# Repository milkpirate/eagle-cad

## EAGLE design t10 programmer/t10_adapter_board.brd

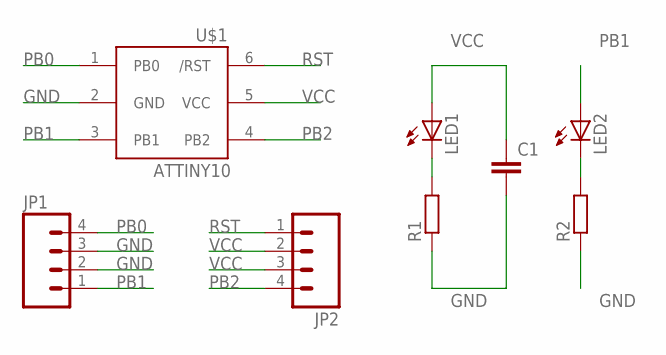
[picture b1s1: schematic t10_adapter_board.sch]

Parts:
C1: C-EUC0805K; C0805K
JP1, JP2: M04PTH; 1X04
LED1, LED2: LEDCHIPLED_0805; CHIPLED_0805
R1, R2: R-EU_R0805; R0805
U$1: ATTINY10; SOT23-6

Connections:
GND: C1.2, JP1.2, JP1.3, R1.1, R2.1, U$1.2 (GND)
unnamed: LED1.C, R1.2
unnamed: LED2.C, R2.2
PB0: JP1.4, U$1.1 (PB0)
PB1: JP1.1, LED2.A, U$1.3 (PB1)
PB2: JP2.4, U$1.4 (PB2)
RST: JP2.1, U$1.6 (/RST)
VCC: C1.1, JP2.2, JP2.3, LED1.A, U$1.5 (VCC)

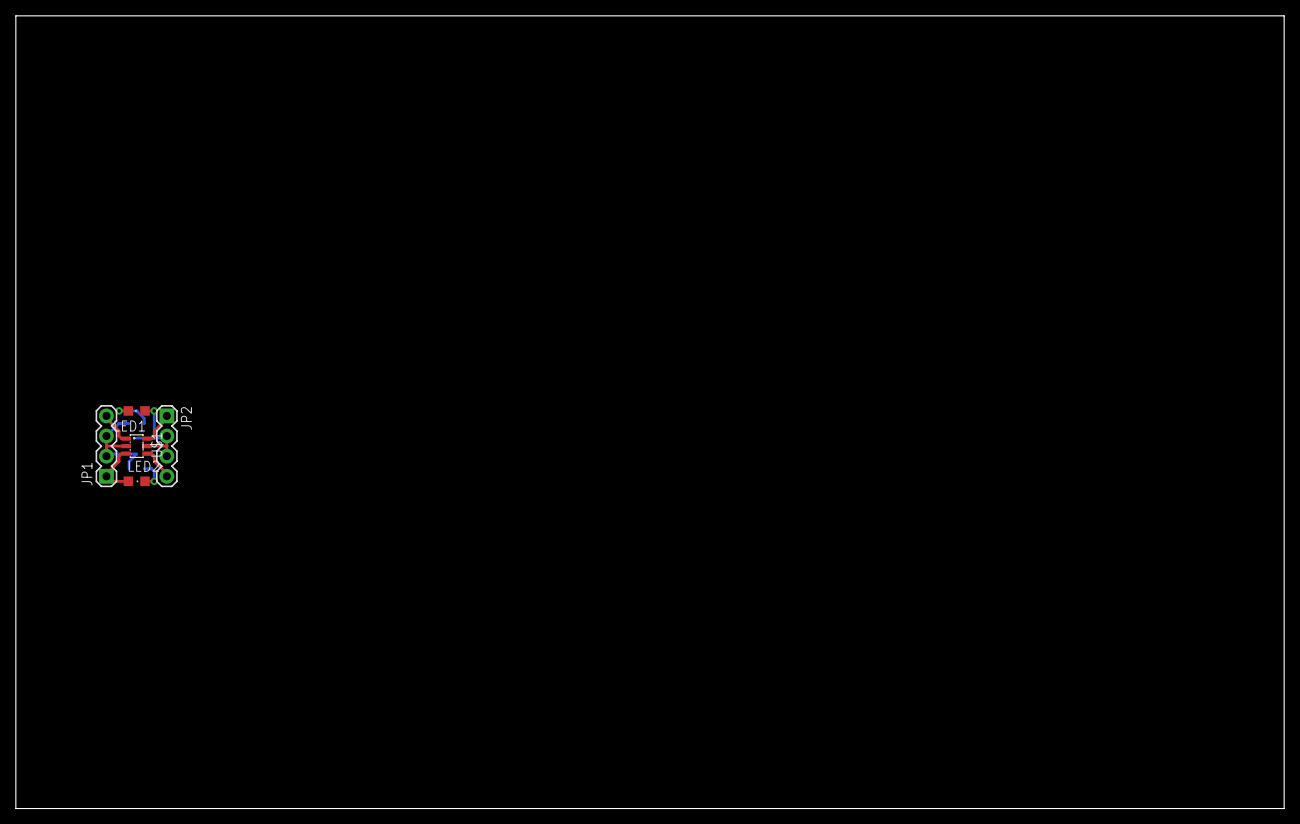
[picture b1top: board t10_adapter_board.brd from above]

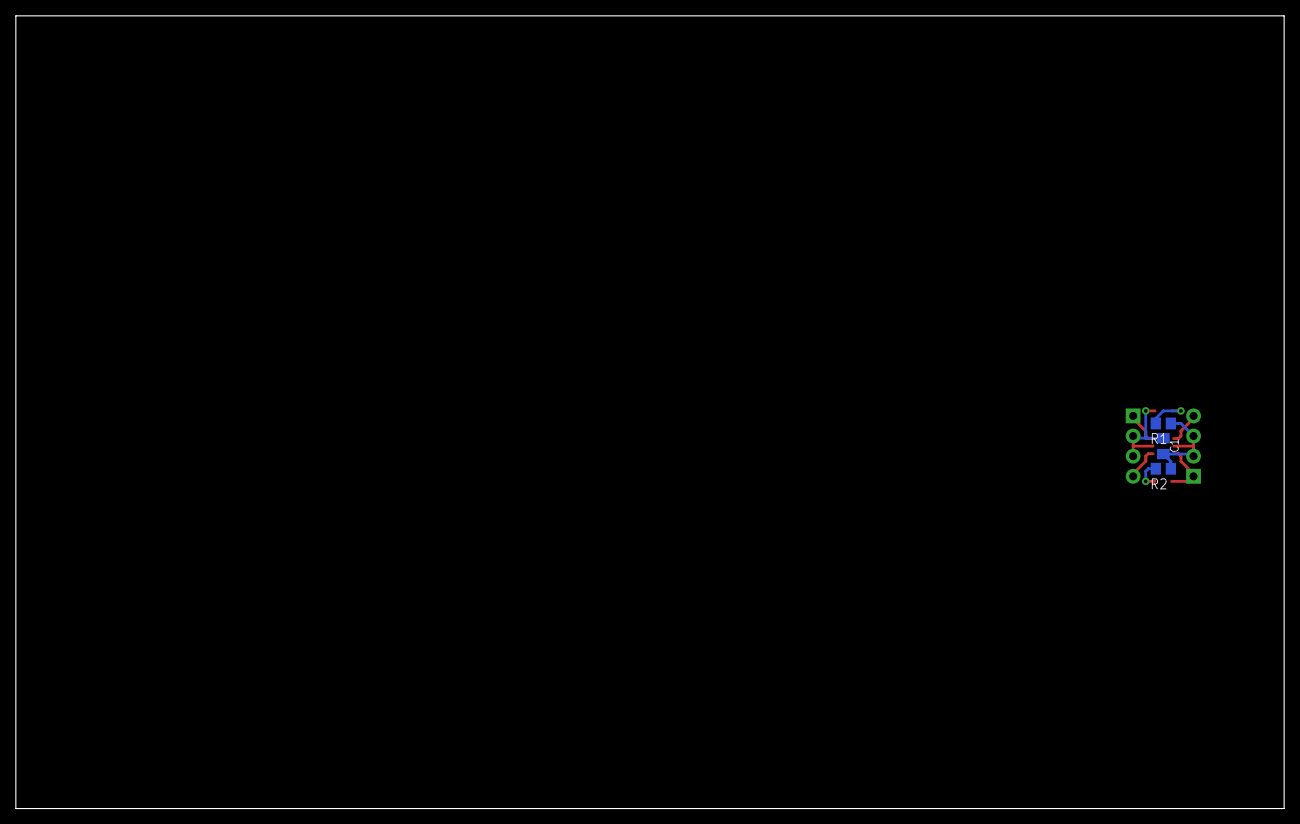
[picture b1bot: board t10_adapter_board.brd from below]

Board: 2 copper layers, 160.0 x 100.0 mm, 8 parts (3 on the bottom side), 8 nets.

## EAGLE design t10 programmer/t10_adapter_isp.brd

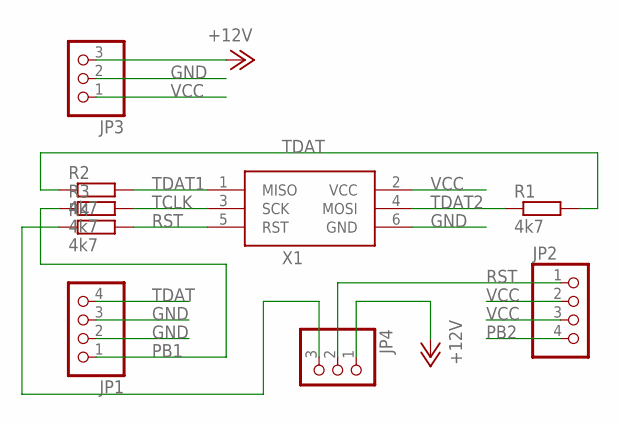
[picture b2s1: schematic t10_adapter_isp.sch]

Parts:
JP1, JP2: PINHD-1X4; 1X04
JP3, JP4: PINHD-1X3; 1X03
R1, R2, R3, R4: 4k7; M0805
X1: AVRISP-HEADER-6-SHROUDED; CONN-HARTING-ML6

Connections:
+12V: JP3.3, JP4.1
GND: JP1.2, JP1.3, JP3.2, X1.6 (GND)
unnamed: JP4.3, R4.1
PB1: JP1.1, R3.1
PB2: JP2.4
RST: JP2.1, JP4.2, R4.2, X1.5 (RST)
TCLK: R3.2, X1.3 (SCK)
TDAT: JP1.4, R1.2, R2.1
TDAT1: R2.2, X1.1 (MISO)
TDAT2: R1.1, X1.4 (MOSI)
VCC: JP2.2, JP2.3, JP3.1, X1.2 (VCC)

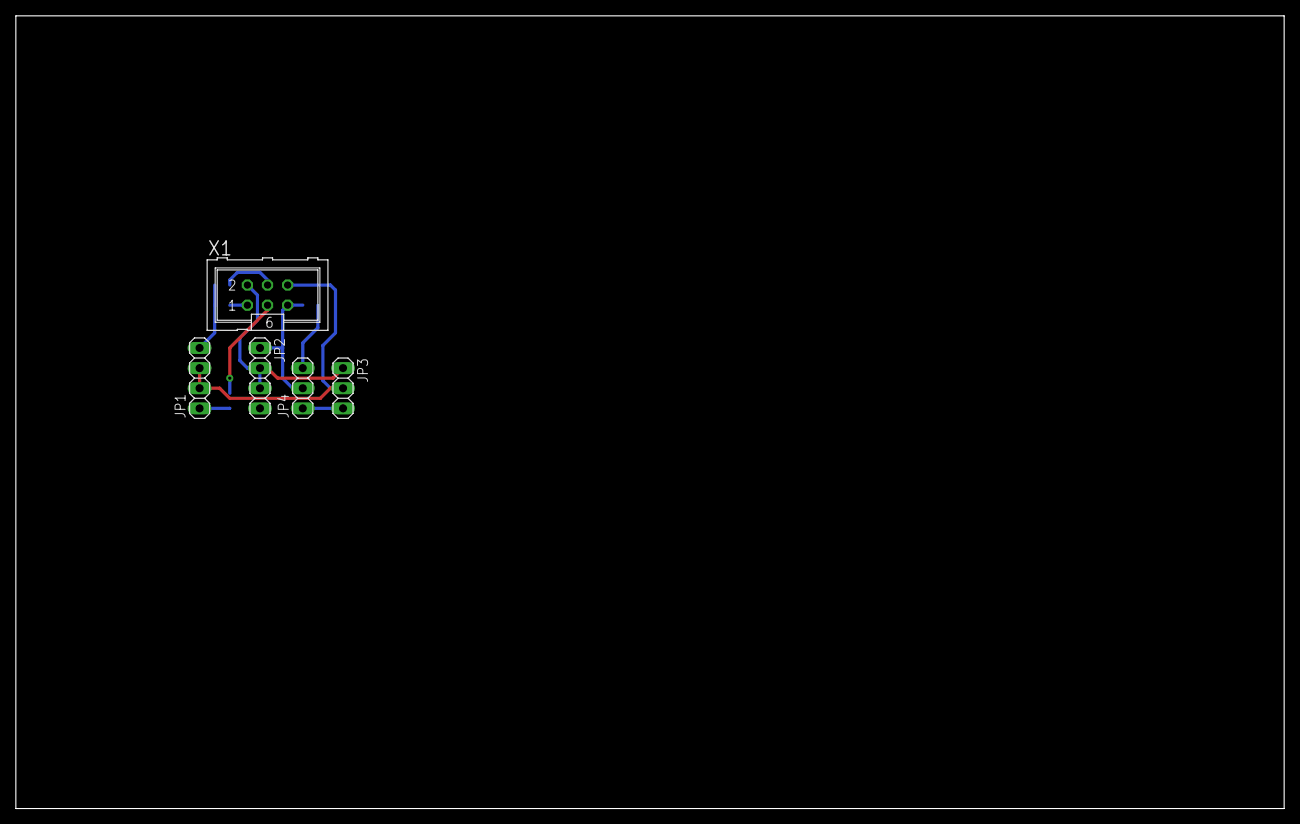
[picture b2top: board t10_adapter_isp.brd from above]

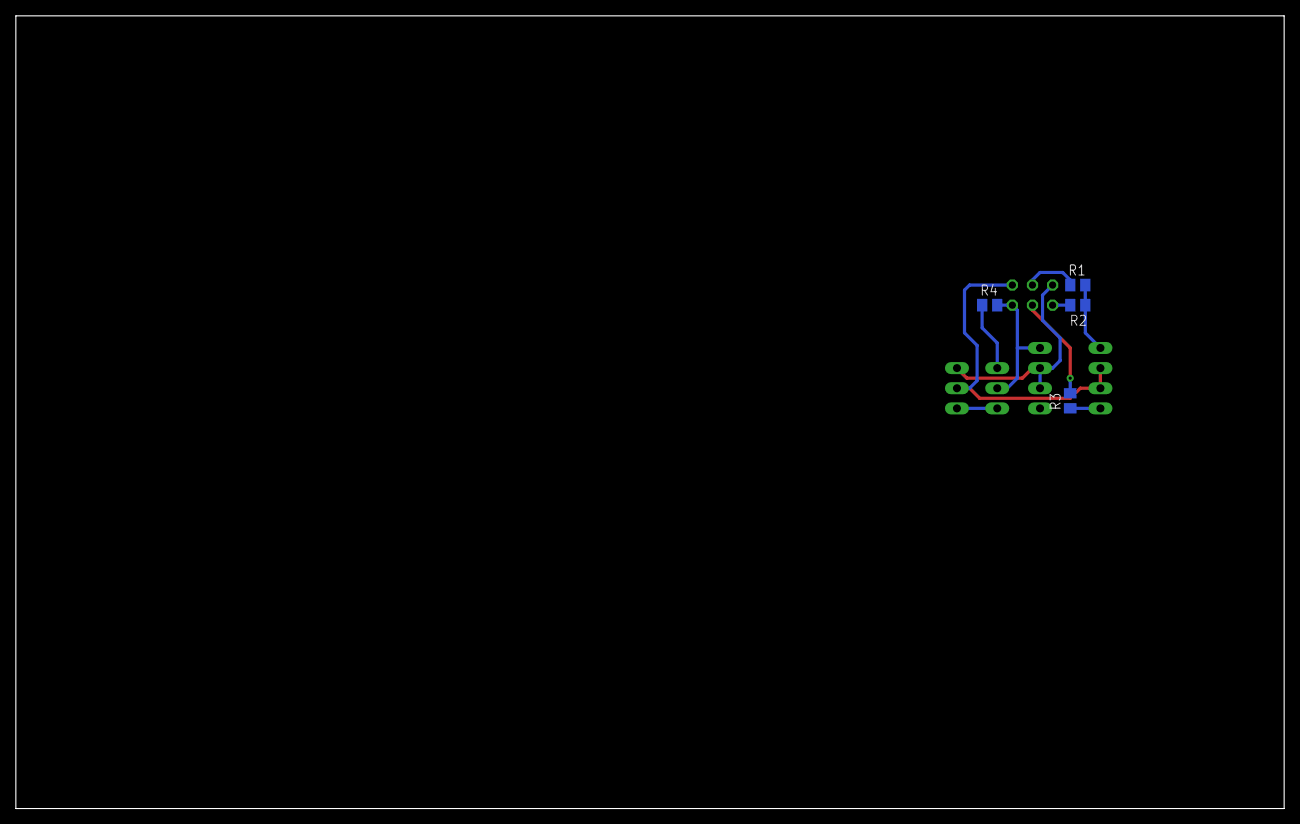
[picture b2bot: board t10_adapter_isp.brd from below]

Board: 2 copper layers, 160.0 x 100.0 mm, 9 parts (4 on the bottom side), 10 nets.

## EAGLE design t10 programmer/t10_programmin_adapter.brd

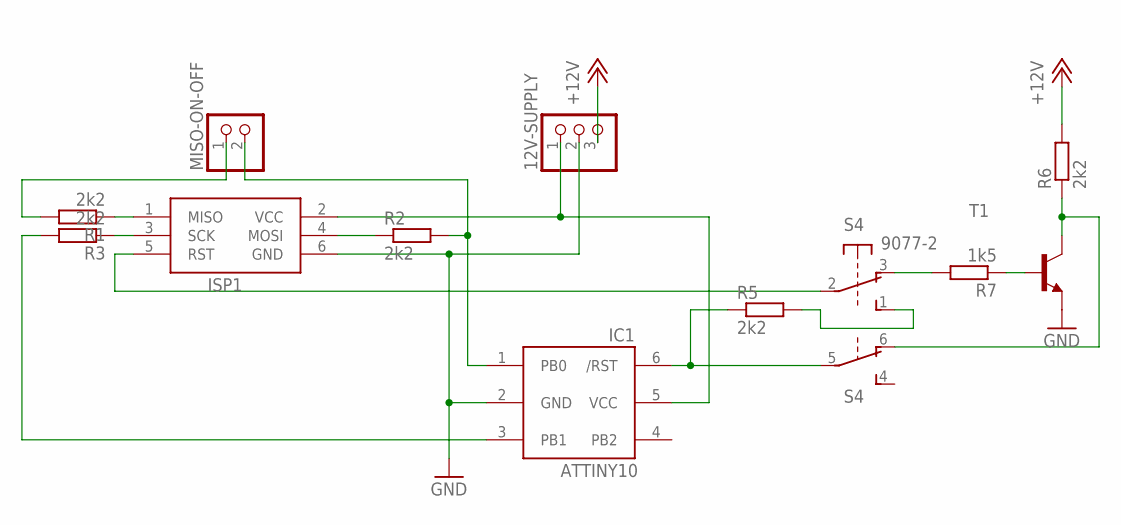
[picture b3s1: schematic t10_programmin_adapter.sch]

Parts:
12V-SUPPLY: PINHD-1X3/90; 1X03/90
IC1: ATTINY10; SOT23-6
ISP1: AVRISP-6; AVRISP
MISO-ON-OFF: PINHD-1X2; 1X02
R1, R2, R3, R5, R6: 2k2; 0204/7
R7: 1k5; 0207/2V
S4: 9077-2
T1: 2N6517-NPN-TO92-CBE; TO92-CBE

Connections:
+12V: 12V-SUPPLY.3, R6.2
GND: 12V-SUPPLY.2, IC1.2 (GND), ISP1.6 (GND), T1.E
ISP-MISO: ISP1.1 (MISO), R1.1
ISP-MOSI: ISP1.4 (MOSI), R2.1
ISP-RST: ISP1.5 (RST), S4.2
ISP-SCK: ISP1.3 (SCK), R3.1
MISO: MISO-ON-OFF.1, R1.2
unnamed: R6.1, S4.6 (O), T1.C
unnamed: R7.1, T1.B
unnamed: R7.2, S4.3 (O)
unnamed: R5.2, S4.1 (S)
RST: IC1.6 (/RST), R5.1, S4.5
SCK: IC1.3 (PB1), R3.2
TDIDATA: IC1.1 (PB0), MISO-ON-OFF.2, R2.2
VCC: 12V-SUPPLY.1, IC1.5 (VCC), ISP1.2 (VCC)

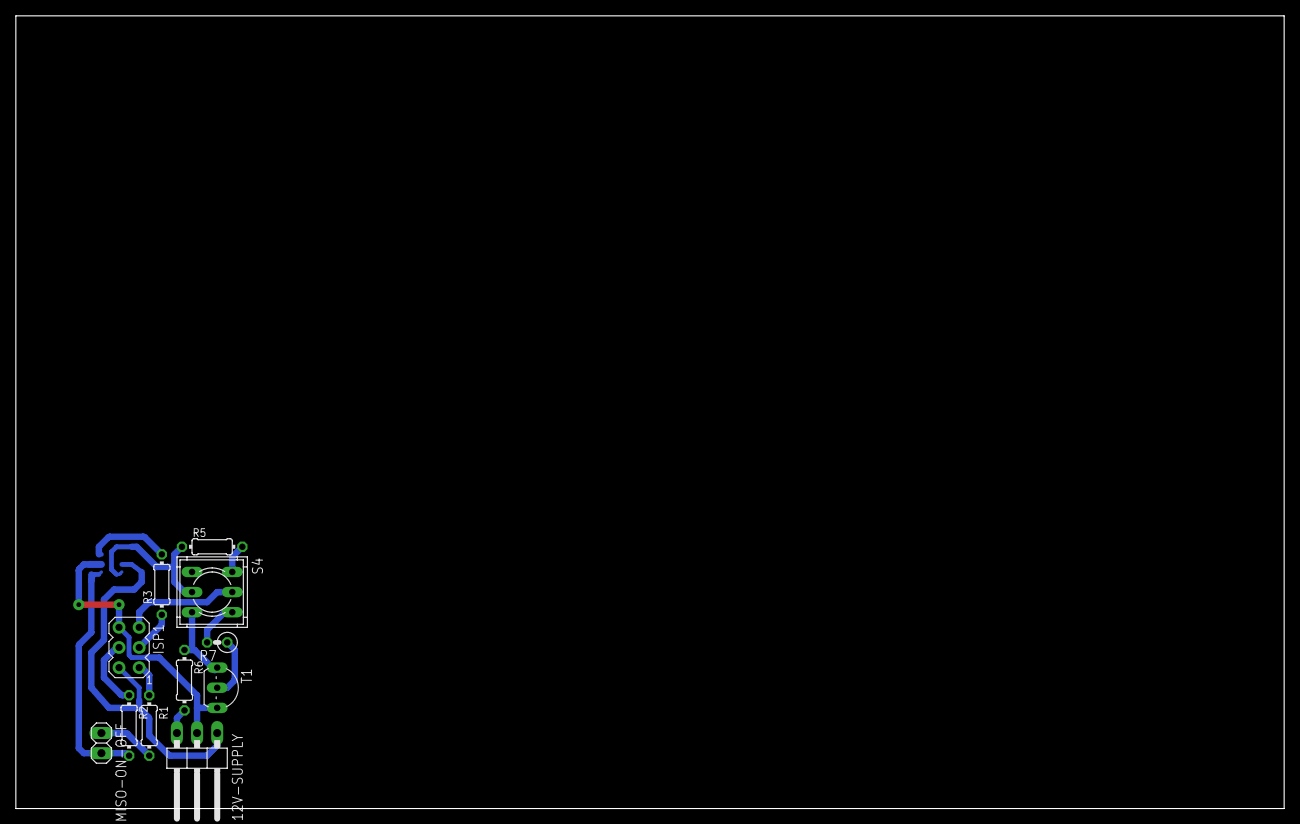
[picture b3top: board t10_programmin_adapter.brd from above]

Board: 2 copper layers, 160.0 x 100.0 mm, 12 parts (1 on the bottom side), 15 nets.

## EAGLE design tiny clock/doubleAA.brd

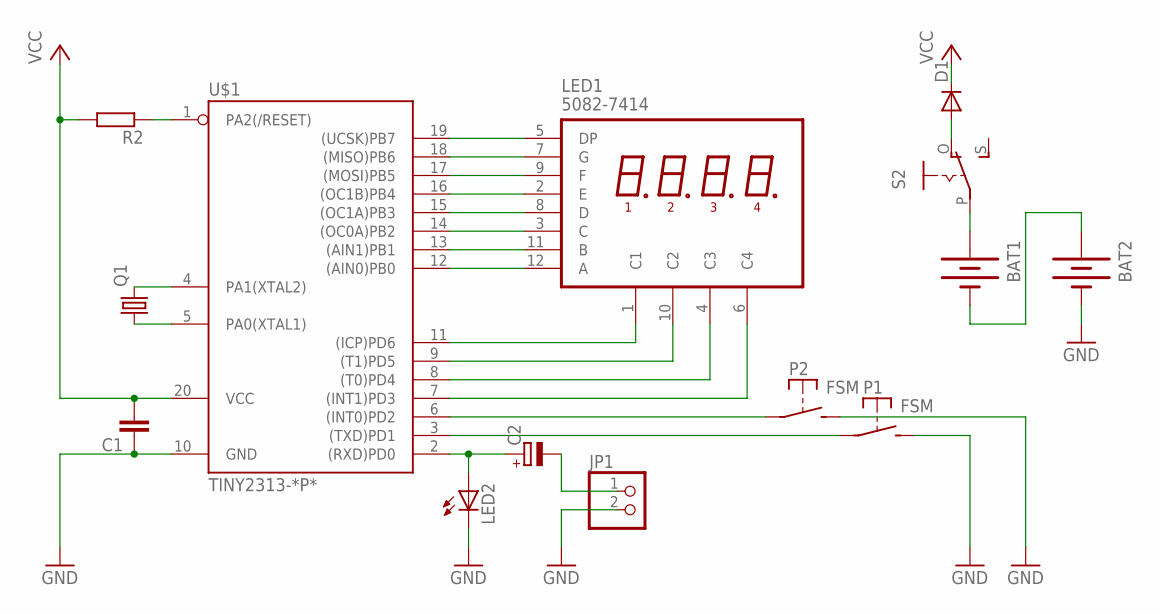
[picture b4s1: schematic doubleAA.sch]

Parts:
BAT1, BAT2: BATTERYAA-PANEL; BATTERY-AA-PANEL
C1: C-EU025-024X044; C025-024X044
C2: CPOL-EUE2,5-6E; E2,5-6E
D1: DIODE-D-5; D-5
JP1: PINHD-1X2; 1X02
LED1: 5082-7414
LED2: LED5MM
P1, P2: FSM
Q1: CRYSTALTC26H; TC26H
R2: R-EU_0204/7; 0204/7
S2: EG1218S; EG1218
U$1: TINY2313-*P*; DIL20

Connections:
GND: BAT2.-, C1.1, JP1.2, LED2.K (C), P1.P$2 (S), P2.P$2 (S), U$1.10 (GND)
unnamed: LED1.5 (DP), U$1.19 ((UCSK)PB7)
unnamed: LED1.7 (G), U$1.18 ((MISO)PB6)
unnamed: LED1.9 (F), U$1.17 ((MOSI)PB5)
unnamed: LED1.2 (E), U$1.16 ((OC1B)PB4)
unnamed: LED1.8 (D), U$1.15 ((OC1A)PB3)
unnamed: LED1.3 (C), U$1.14 ((OC0A)PB2)
unnamed: LED1.11 (B), U$1.13 ((AIN1)PB1)
unnamed: LED1.12 (A), U$1.12 ((AIN0)PB0)
unnamed: LED1.1 (C1), U$1.11 ((ICP)PD6)
unnamed: LED1.10 (C2), U$1.9 ((T1)PD5)
unnamed: LED1.4 (C3), U$1.8 ((T0)PD4)
unnamed: LED1.6 (C4), U$1.7 ((INT1)PD3)
unnamed: Q1.2, U$1.4 (PA1(XTAL2))
unnamed: Q1.1, U$1.5 (PA0(XTAL1))
unnamed: P2.P$1, U$1.6 ((INT0)PD2)
unnamed: P1.P$1, U$1.3 ((TXD)PD1)
unnamed: R2.1, U$1.1 (PA2(/RESET))
unnamed: BAT1.+, S2.P
unnamed: C2.+, LED2.A, U$1.2 ((RXD)PD0)
unnamed: C2.-, JP1.1
unnamed: D1.A, S2.O
unnamed: BAT1.-, BAT2.+
VCC: C1.2, D1.C, R2.2, U$1.20 (VCC)

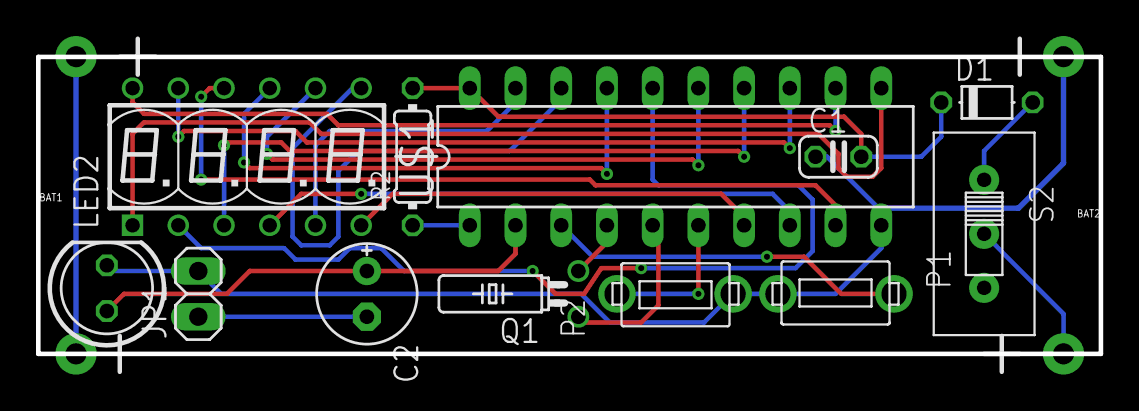
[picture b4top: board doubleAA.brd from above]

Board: 2 copper layers, 59.0 x 16.5 mm, 14 parts (0 on the bottom side), 24 nets.

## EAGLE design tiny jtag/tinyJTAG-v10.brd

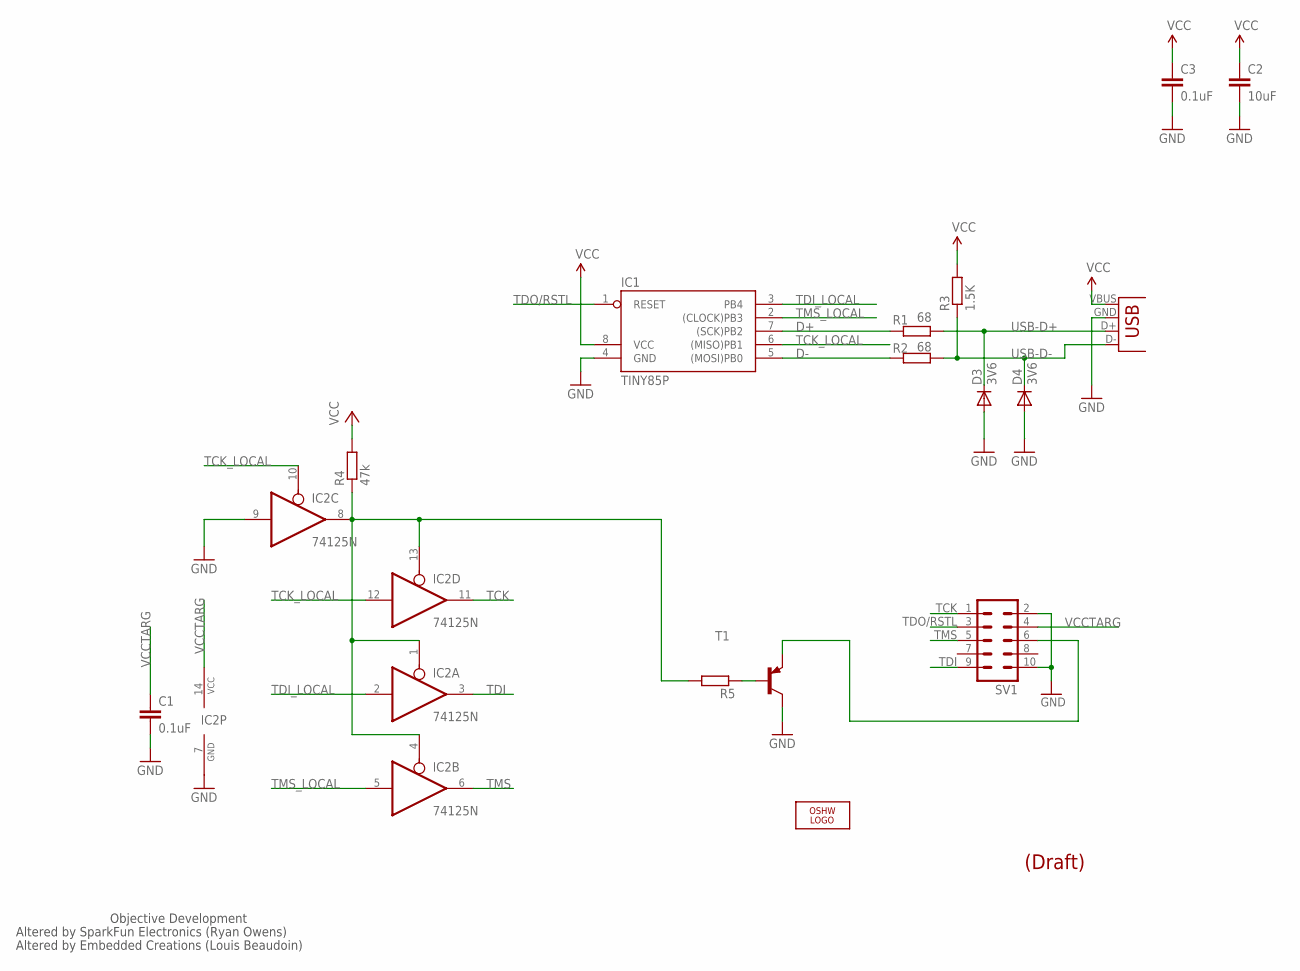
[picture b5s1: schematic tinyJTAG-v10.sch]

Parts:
C1: 0.1uF; CAP-PTH-SMALL2
C2: 10uF; C025-025X050
C3: 0.1uF; CAP-PTH-SMALL
D3: 3V6; D-2.5
D4: 3V6; D-5
IC1: TINY85P; DIL08
IC2: 74125N; DIL14
LOGO1: OSHW_LOGO_FILLX0150-NT; OSHW_FILLX150_NOTEXT
R1, R2: 68; 0207/2V
R3: 1.5K; 0207/2V
R4: 47k; 0207/7
R5: R-EU_0207/7; 0207/7
SV1: ML10
T1: BC327-16-PNP-TO92-EBC; TO92-EBC
X1: USB-A-H

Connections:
D+: IC1.7 ((SCK)PB2), R1.2
D-: IC1.5 ((MOSI)PB0), R2.2
GND: C1.2, C2.2, C3.2, D3.A, D4.A, IC1.4 (GND), IC2.7 (GND), IC2.9 (I), SV1.2, SV1.10, T1.C, X1.GND (VBUS)
unnamed: IC2.1 (OE), IC2.4 (OE), IC2.8 (O), IC2.13 (OE), R4.1, R5.2
unnamed: SV1.6, T1.E
unnamed: R5.1, T1.B
TCK: IC2.11 (O), SV1.1
TCK_LOCAL: IC1.6 ((MISO)PB1), IC2.10 (OE), IC2.12 (I)
TDI: IC2.3 (O), SV1.9
TDI_LOCAL: IC1.3 (PB4), IC2.2 (I)
TDO/RSTL: IC1.1 (RESET), SV1.3
TMS: IC2.6 (O), SV1.5
TMS_LOCAL: IC1.2 ((CLOCK)PB3), IC2.5 (I)
USB-D+: D3.C, R1.1, X1.D+ (D-)
USB-D-: D4.C, R2.1, R3.1, X1.D- (D+)
VCC: C2.1, C3.1, IC1.8 (VCC), R3.2, R4.2, X1.VBUS (GND)
VCCTARG: C1.1, IC2.14 (VCC), SV1.4

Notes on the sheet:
Objective Development
Altered by SparkFun Electronics (Ryan Owens)
Altered by Embedded Creations (Louis Beaudoin)
(Draft)

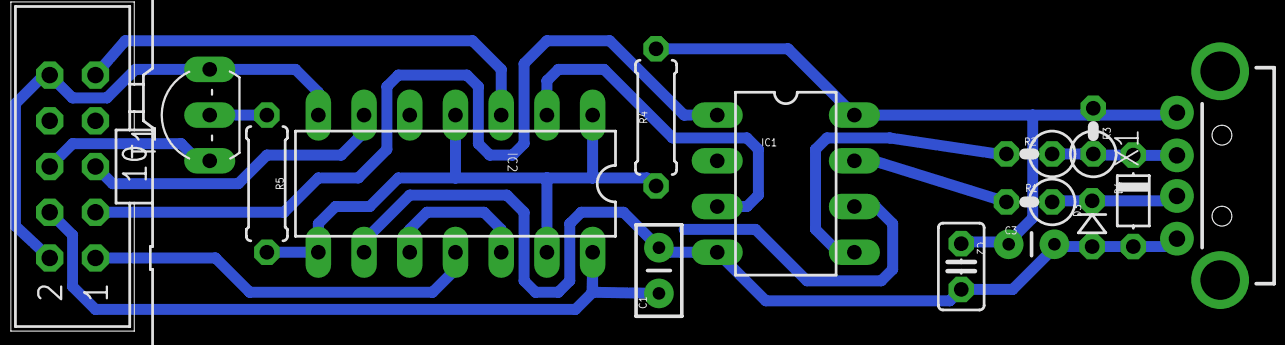
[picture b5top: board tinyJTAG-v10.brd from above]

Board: 2 copper layers, 16 parts (1 on the bottom side), 17 nets.

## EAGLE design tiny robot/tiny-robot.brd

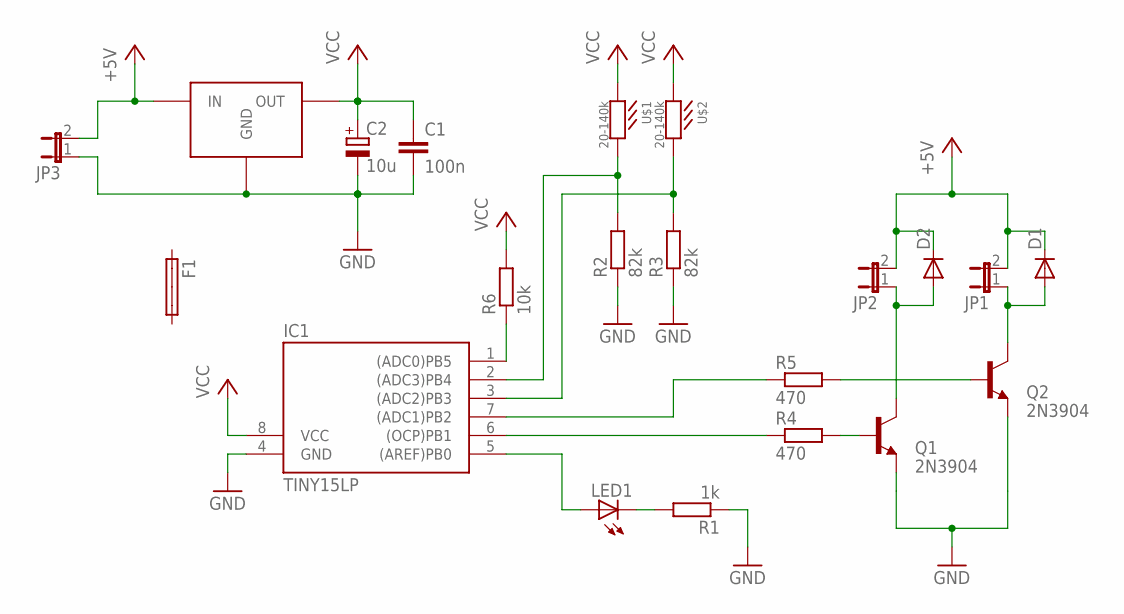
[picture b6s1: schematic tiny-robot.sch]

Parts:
C1: 100n; C025-025X050
C2: 10u; E2,5-6E
D1, D2: 1N4148DO35-7; DO35-7
F1: SHK20L
IC1: TINY15LP; DIL08
JP1, JP2, JP3: JP1E; JP1
LED1: LED3MM
Q1, Q2: 2N3904; TO92
R1: 1k; 0207/2V
R2, R3: 82k; 0207/5V
R4: 470; 0207/2V
R5: 470; 0207/5V
R6: 10k; 0207/5V
U$1, U$2: 20-140k; LDR-906014
U$3: MCP1700; TO92

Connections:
+5V: D1.C, D2.C, JP1.2, JP2.2, JP3.2, U$3.2 (IN)
GND: C1.2, C2.-, IC1.4 (GND), JP3.1, Q1.3 (E), Q2.3 (E), R1.1, R2.1, R3.1, U$3.3 (GND)
MISO: IC1.6 ((OCP)PB1), R4.1
MOSI: IC1.5 ((AREF)PB0), LED1.A
unnamed: LED1.K (C), R1.2
unnamed: Q1.2 (B), R4.2
unnamed: Q2.2 (B), R5.2
unnamed: D2.A, JP2.1, Q1.1 (C)
unnamed: D1.A, JP1.1, Q2.1 (C)
unnamed: IC1.3 ((ADC2)PB3), R3.2, U$2.P$2
unnamed: IC1.2 ((ADC3)PB4), R2.2, U$1.P$2
RST: IC1.1 ((ADC0)PB5), R6.1
SCK: IC1.7 ((ADC1)PB2), R5.1
VCC: C1.1, C2.+, IC1.8 (VCC), R6.2, U$1.P$1, U$2.P$1, U$3.1 (OUT)

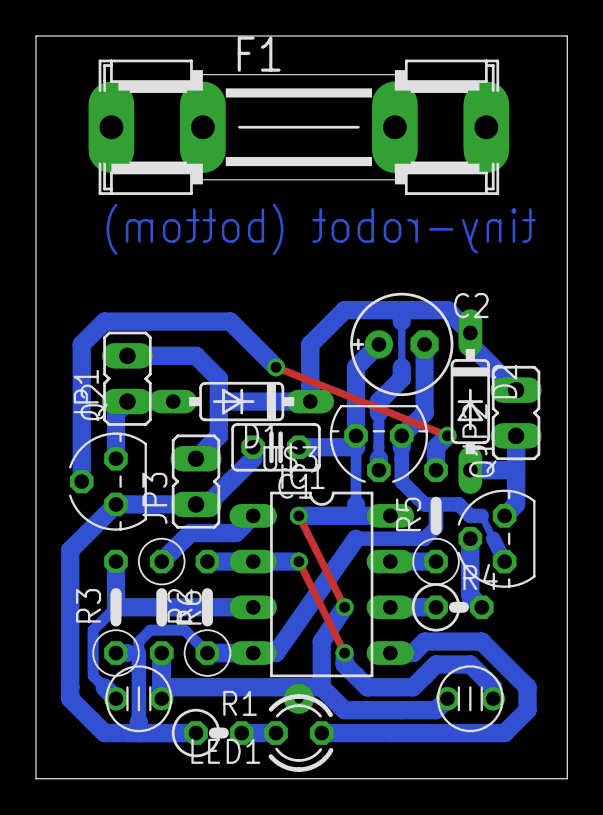
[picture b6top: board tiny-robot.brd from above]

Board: 2 copper layers, 29.5 x 41.3 mm, 21 parts (0 on the bottom side), 14 nets.

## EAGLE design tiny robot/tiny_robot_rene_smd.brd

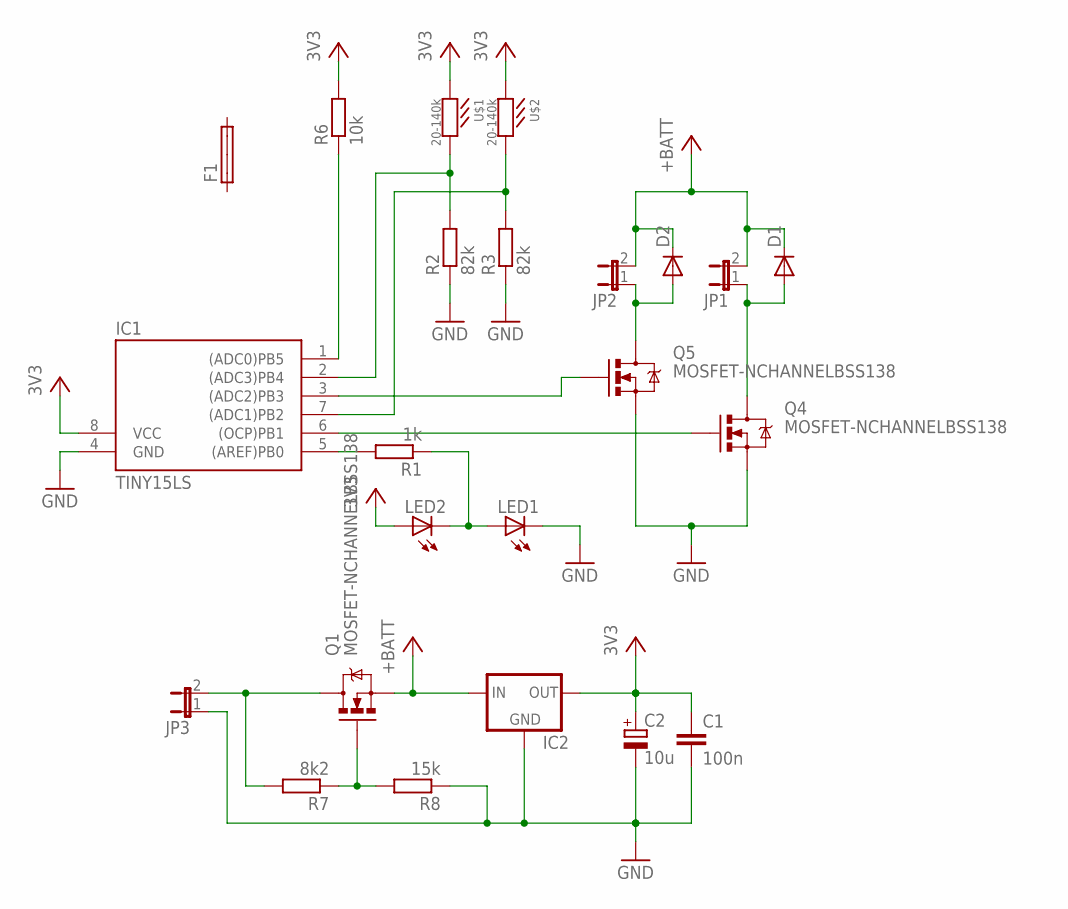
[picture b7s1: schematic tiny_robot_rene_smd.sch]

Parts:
C1: 100n; C0805K
C2: 10u; SANYO-OSCON_SMD_A5
D1, D2: DIODE-MINIMELF; MINIMELF
F1: SHK20L
IC1: TINY15LS; SOIC8
IC2: MCP1700SMD; SOT23
JP1, JP2, JP3: JP1E; JP1
LED1, LED2: LEDCHIPLED_0805; CHIPLED_0805
Q1, Q4, Q5: MOSFET-NCHANNELBSS138; SOT23
R1: 1k; M1206
R2, R3: 82k; M1206
R6: 10k; M1206
R7: 8k2; M0805
R8: 15k; M0805
U$1, U$2: 20-140k; LDR-906014

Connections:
+5V: D1.C, D2.C, IC2.3 (IN), JP1.2, JP2.2, Q1.2 (S)
GND: C1.2, C2.-, IC1.4 (GND), IC2.1 (GND), JP3.1, LED1.C, Q4.2 (S), Q5.2 (S), R2.1, R3.1, R8.1
unnamed: JP3.2, Q1.3 (D), R7.2
unnamed: IC1.5 ((AREF)PB0), R1.2
unnamed: IC1.6 ((OCP)PB1), Q4.1 (G)
unnamed: LED1.A, LED2.C, R1.1
unnamed: Q1.1 (G), R7.1, R8.2
unnamed: IC1.3 ((ADC2)PB3), Q5.1 (G)
unnamed: D2.A, JP2.1, Q5.3 (D)
unnamed: D1.A, JP1.1, Q4.3 (D)
unnamed: IC1.7 ((ADC1)PB2), R3.2, U$2.P$2
unnamed: IC1.2 ((ADC3)PB4), R2.2, U$1.P$2
RST: IC1.1 ((ADC0)PB5), R6.1
VCC: C1.1, C2.+, IC1.8 (VCC), IC2.2 (OUT), LED2.A, R6.2, U$1.P$1, U$2.P$1

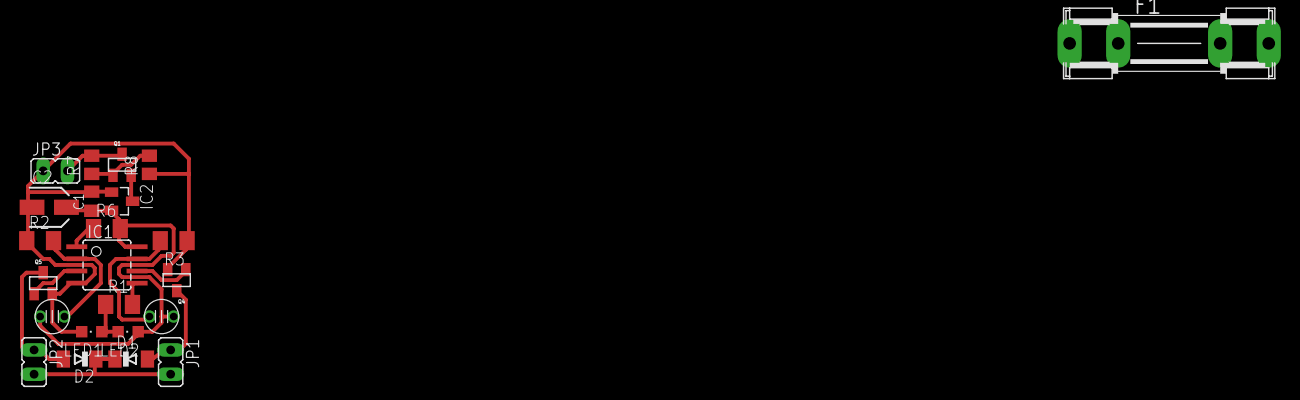
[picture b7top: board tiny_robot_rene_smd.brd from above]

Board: 2 copper layers, 23 parts (0 on the bottom side), 14 nets.

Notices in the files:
parts and their libraries:
SparkFun-Connectors: Licensing: Creative Commons ShareAlike 4.0 International - https://creativecommons.org/licenses/by-sa/4.0
SparkFun-DiscreteSemi: Licensing: CC v3.0 Share-Alike You are welcome to use this library for commercial purposes.
